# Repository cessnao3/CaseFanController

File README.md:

# Case Fan Controller

This case fan contrtoller is designed to convert from a 4-pin PWM output into a 2/3-pin voltage fan setup.
The goal is to allow the motherboard to control the fan speed just as if the fans were traditional 4-pin PWM fans.

## Components

The components for the board include:
* PCB (per the `pcb` folder)
* Sparkfun Dual TB6612FNG Motor Controller
* Logic Level Converter
* Raspberry Pi Pico
* Case (per the `case` folder), optional
* Spare molex power input
* 3-pin fan header (two, optionally)

## Software

In order to perform the transformation between the PWM and voltage signals, the Raspberry Pi Pico reads the duty cycle of the PWM, between 0.0 and 1.0, and transforms it into a duty cycle to send to the motor controller. This is a linear relation, so 30% duty cycle from the motherboard will equate 30% of the full 12 V signal. This runs at 10 Hz.

If the PWM duty cycle is below 10%, the motors shut off.

As the chosen motor controller has a 1.2 A limit on each channel output, both channels are brought out and controlled, in mirror, allowing for a total of 2.4 A to go to all attached motors.

It was envisioned that some sort of "start-up" would be needed to facilitate starting/stopping the motors, but this has not been necessary in practice thus far.

## PCB

The PCB schematic is shown below.

## Future Work

After the first revision of the board, several improvements were identified that would improve the process for future revisions. These are provided below.

* Move pins from 0/1/2 to other available pins make room for UART
* Add UART output, provide dedicated pins for tx/rx/gnd
* Move pin 18 -> 19 for channel B PWM input, Move 19 -> New PWB Slice, for tach output

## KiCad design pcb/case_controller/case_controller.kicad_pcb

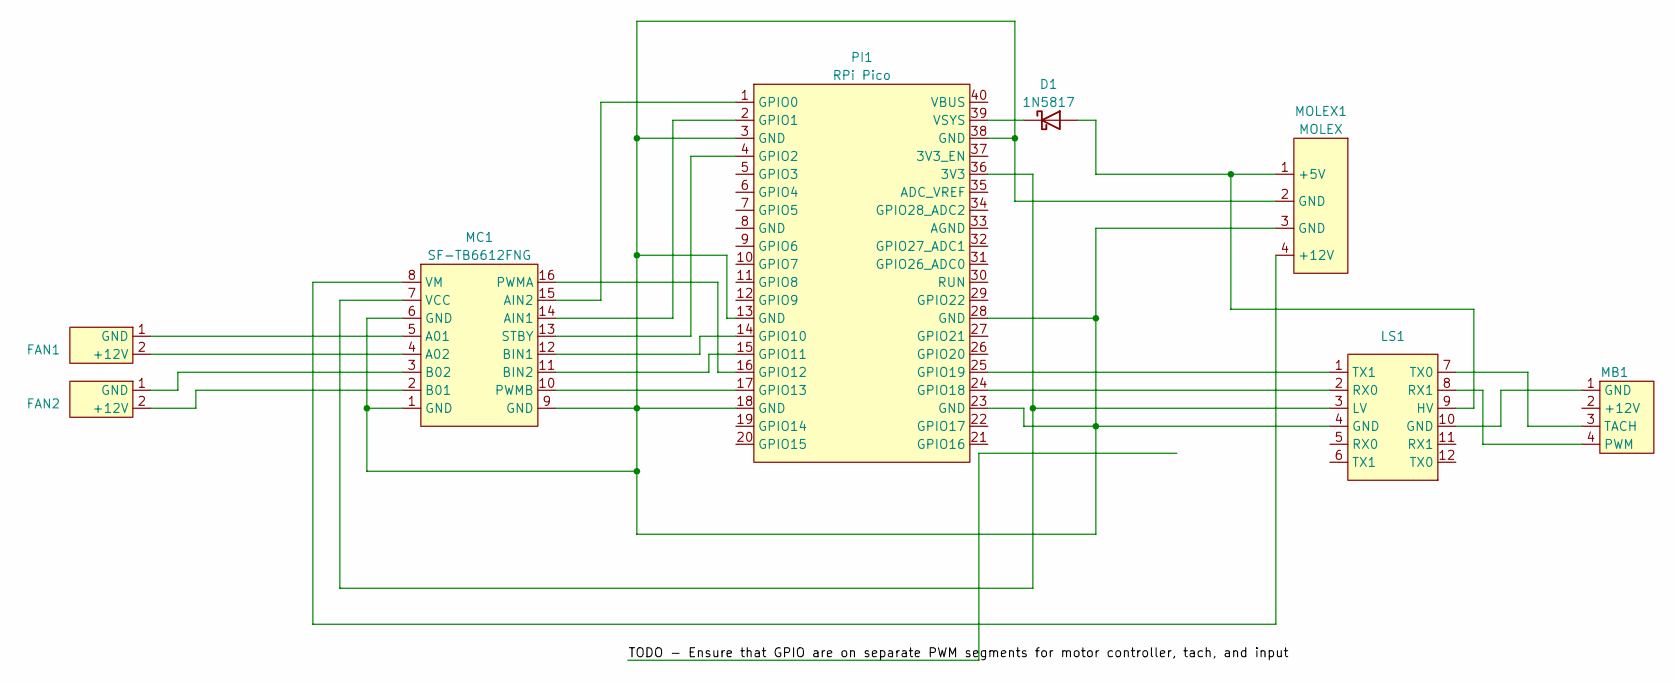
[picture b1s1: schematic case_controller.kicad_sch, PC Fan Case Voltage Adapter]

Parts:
D1: 1N5817; D_DO-41_SOD81_P10.16mm_Horizontal
FAN1, FAN2: Fan Connector
LS1: Level_Shifter
MB1: MB_Fan_Header
MC1: SF-TB6612FNG
MOLEX1: MOLEX; Molex Connector
PI1: RPi Pico

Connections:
unnamed: D1.2 (A), LS1.9 (HV), MOLEX1.1 (+5V)
unnamed: D1.1 (K), PI1.39 (VSYS)
unnamed: FAN1.2 (+12V), MC1.4 (A02)
unnamed: FAN1.1 (GND), MC1.5 (A01)
unnamed: FAN2.2 (+12V), MC1.2 (B01)
unnamed: FAN2.1 (GND), MC1.3 (B02)
unnamed: LS1.4 (GND), MC1.1 (GND), MC1.6 (GND), MC1.9 (GND), MOLEX1.2 (GND), MOLEX1.3 (GND), PI1.3 (GND), PI1.13 (GND), PI1.18 (GND), PI1.23 (GND), PI1.28 (GND), PI1.38 (GND)
unnamed: LS1.3 (LV), MC1.7 (VCC), PI1.36 (3V3)
unnamed: LS1.10 (GND), MB1.1 (GND)
unnamed: LS1.8 (RX1), MB1.4 (PWM)
unnamed: LS1.7 (TX0), MB1.3 (TACH)
unnamed: MC1.14 (AIN1), PI1.2 (GPIO1)
unnamed: MC1.15 (AIN2), PI1.1 (GPIO0)
unnamed: MC1.12 (BIN1), PI1.14 (GPIO10)
unnamed: MC1.11 (BIN2), PI1.15 (GPIO11)
unnamed: MC1.16 (PWMA), PI1.16 (GPIO12)
unnamed: MC1.10 (PWMB), PI1.17 (GPIO13)
unnamed: MC1.13 (STBY), PI1.4 (GPIO2)
unnamed: MC1.8 (VM), MOLEX1.4 (+12V)
unnamed: LS1.2 (RX0), PI1.24 (GPIO18)
unnamed: LS1.1 (TX1), PI1.25 (GPIO19)

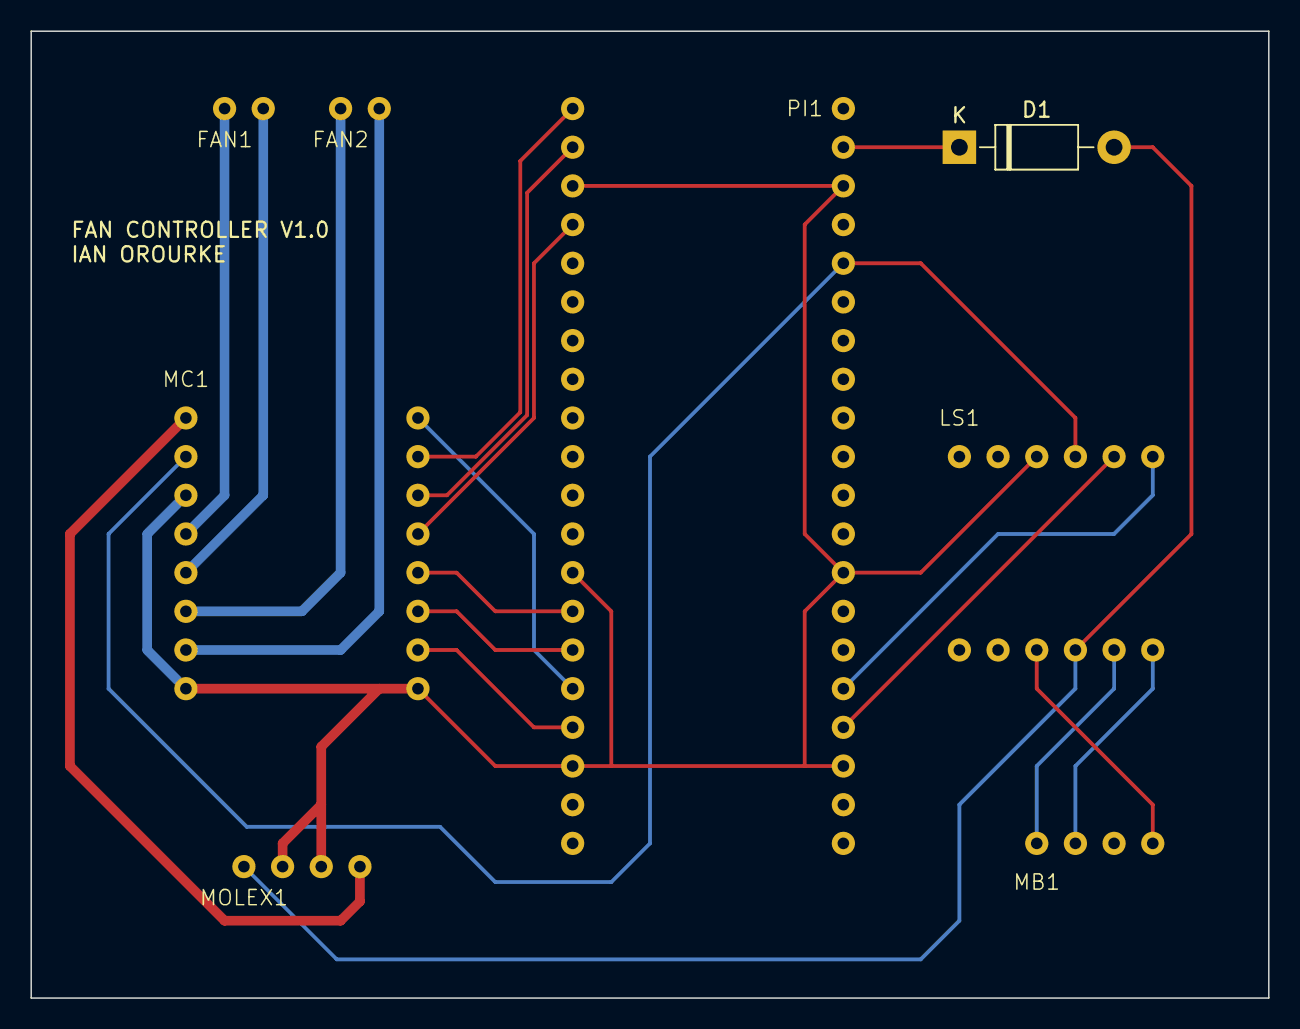
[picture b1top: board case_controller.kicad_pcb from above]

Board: 2 copper layers, 81.3 x 63.5 mm, 8 parts (0 on the bottom side), 21 nets.

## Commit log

2023-05-14 Add comments
2023-07-04 Update TODO
2023-07-04 Final v1.0
2024-01-02 Don't include lock files
2024-01-02 Initial commit for controller
2024-01-03 Split into additional files
2024-01-03 Initial working PWM
2024-01-03 Updates to PWM init
2024-01-04 Update main for basic PWM reading
2024-01-04 Working fan controller!
2024-01-04 Add readme
2024-01-04 Add initial enclosure CAD
2024-01-05 Update fan controllerto be a straight passthrough
2024-01-06 Add documentation
2024-01-08 Model updates
2024-01-20 Add rate controller
